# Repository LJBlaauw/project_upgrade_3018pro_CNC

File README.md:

# project_upgrade_3018pro_CNC

Het project is gebaseerd op opensource tools:
 - Freecad (3D parametrichs CAD)
 - Prusa slicer (3D printables voor Z unit en moerhouders
 - Kicad (PCB CAD ontwerp pico CNC, firmware GRBL webbuilder)
 - librecad (2D CAD)
 - GRBLHAL (GRBL uitbreiding voor diverse 32 bit processors)

# Dit project heft de tekort komingen van de Vevor S3018 Pro Max op

 1. Niet stijf genoeg De RVS geleiders buigen door.
 2. De Aluminium plaat is niet vlak.
 3. De spindel motor heeft een te klein vermogen.
 4. De gebruikte controller heeft de in en uitgangen direct naar buiten uitgevoerd, gevoelig voor storing.
 5. Geen eindschakelaars voor rustpositie.
 6. Te lichte XYZ motoren.
 7. Ondersteunt alleen GRBL.
 8. De moeren hebben backlash bij belasting.
 9. Geen Z-probe ingang
 10. Geen mist of Flood aansluiting

# aanpassingen

 1. Maakt gebruik van aluminium profielen en lineaire rails met blokken.
 2. gebruikt een vlakke stijve kunstof basis plaat.
 3. Maakt gebruik van een borstelloze spindle motor.
 4. Alle in en uitgangen worden gebufferd.
 5. WYZ eindschakelaars worden toegevoegd.
 6. De XYZmotoren zijn door zwaardere typen vervangen.
 7. Er is een nieuwe controller pico-CNC/GRBLHAL toegevoegd (RP2040 of RP2350, 64 bit).
 8. De XYZ-moeren worden nu gesteld zodat er geen backlash meer is.
 9. Aansluiting voor een touch plate of direct met de spindle
 10. ER zijn twee solid state uitgangen die direct uit de CNC router software aangestuurd kunnen worden.

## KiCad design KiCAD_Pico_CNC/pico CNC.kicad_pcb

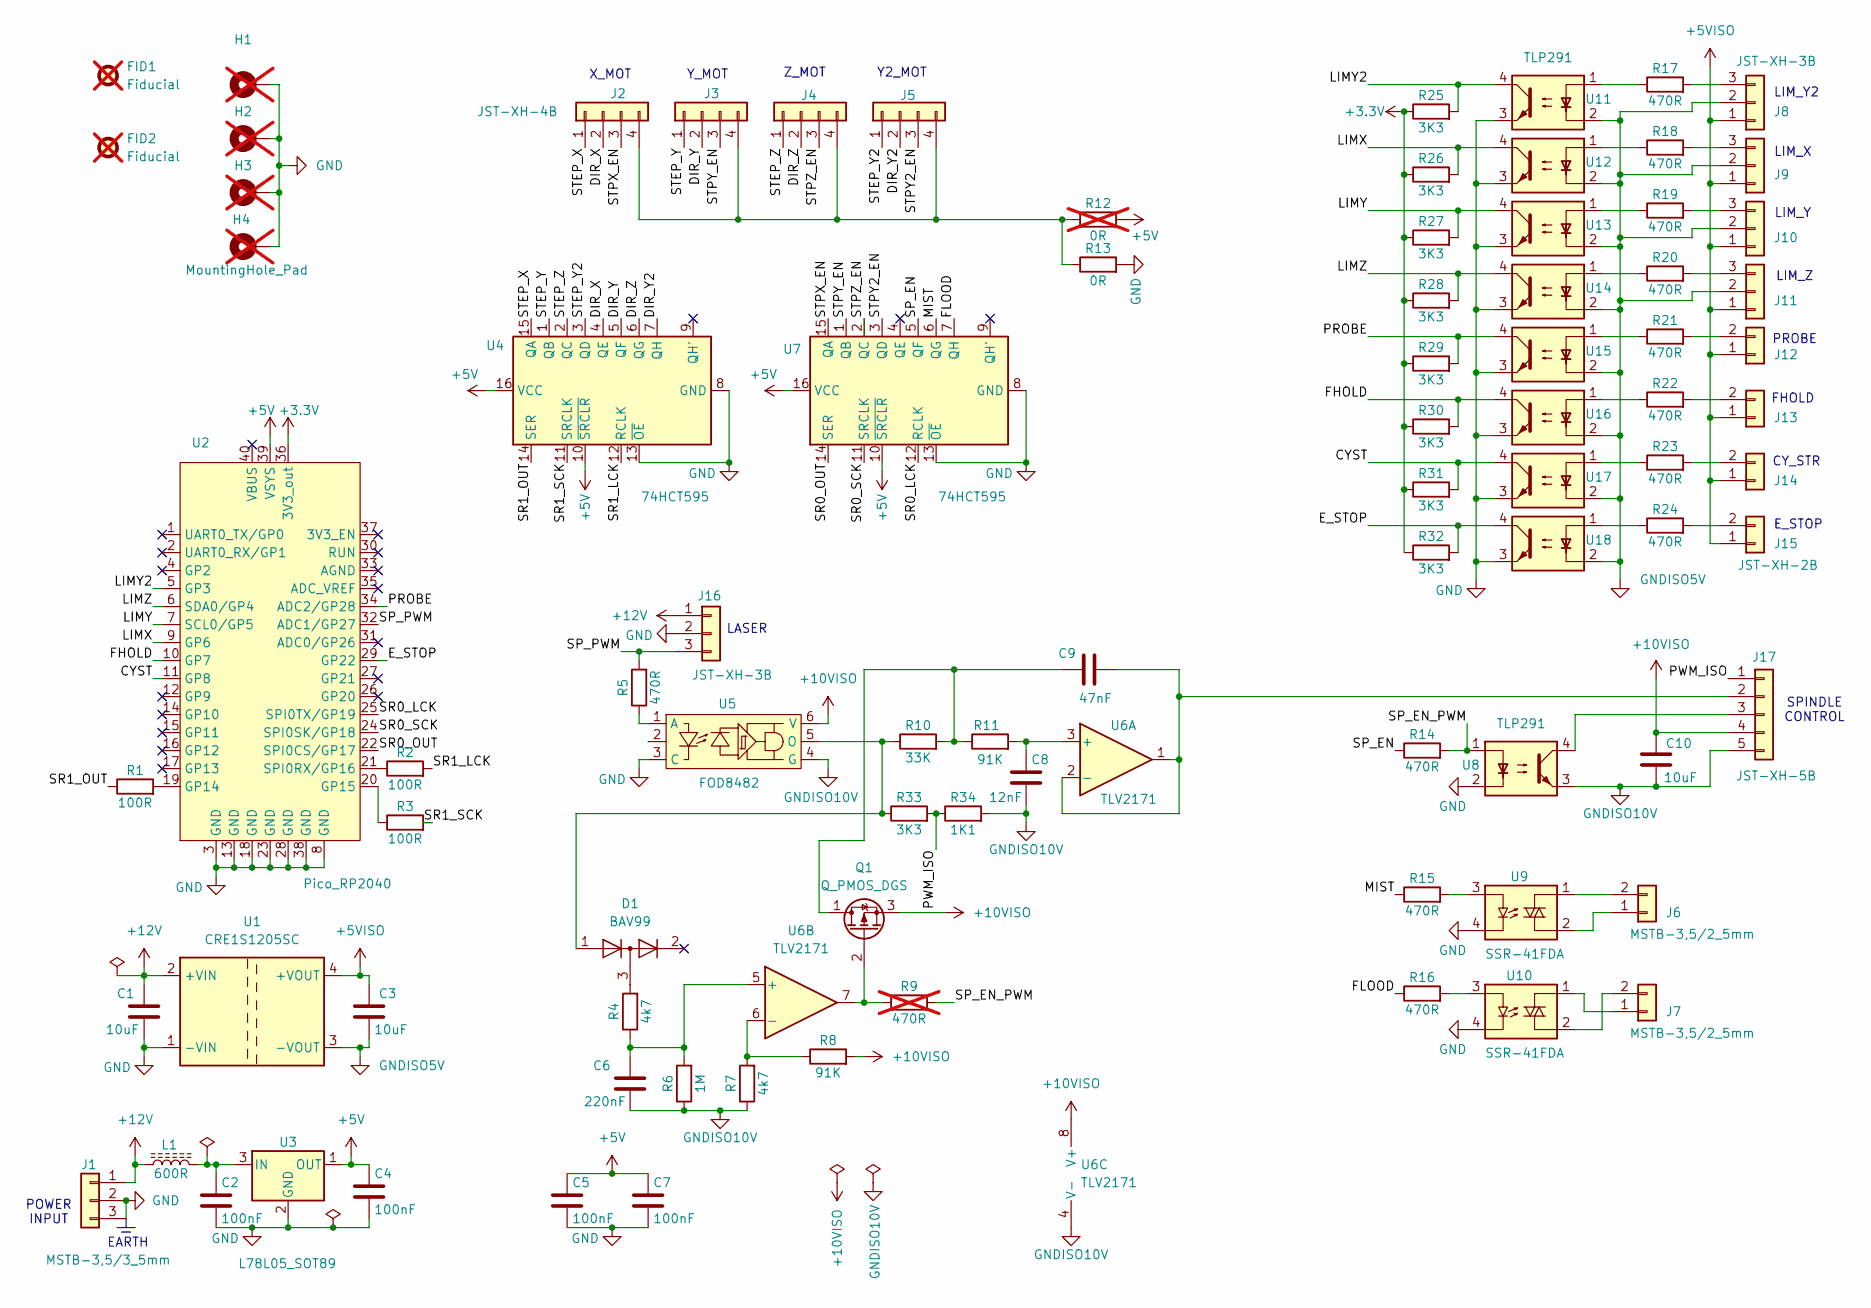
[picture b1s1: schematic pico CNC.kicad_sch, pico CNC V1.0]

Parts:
C1, C3, C10: 10uF; C_1206_3216Metric
C2, C4, C5, C7: 100nF; C_0805_2012Metric
C6: 220nF; C_0805_2012Metric
C8: 12nF; C_0805_2012Metric
C9: 47nF; C_0805_2012Metric
D1: BAV99; SOT-23
FID1, FID2: Fiducial; Fiducial_1mm_Mask2mm; not fitted
H1, H2, H3, H4: MountingHole_Pad; MountingHole_3.2mm_M3_Pad_Via; not fitted
J1: MSTB-3,5/3_5mm; PhoenixContact_MSTBA_2,5_3-G_1x03_P5.00mm_Horizontal
J2, J3, J4, J5: JST-XH-4B; JST_XH_B4B-XH-A_1x04_P2.50mm_Vertical
J6, J7: MSTB-3,5/2_5mm; PhoenixContact_MSTBA_2,5_2-G_1x02_P5.00mm_Horizontal
J8, J9, J10, J11, J16: JST-XH-3B; JST_XH_B3B-XH-A_1x03_P2.50mm_Vertical
J12, J13, J14, J15: JST-XH-2B; JST_XH_B2B-XH-A_1x02_P2.50mm_Vertical
J17: JST-XH-5B; JST_XH_B5B-XH-A_1x05_P2.50mm_Vertical
L1: 600R; L_0805_2012Metric
Q1: Q_PMOS_DGS
R1, R2, R3: 100R; R_0805_2012Metric
R4, R7: 4k7; R_0805_2012Metric
R5, R14, R15, R16, R17, R18, R19, R20, R21, R22, R23, R24: 470R; R_0805_2012Metric
R6: 1M; R_0805_2012Metric
R8, R11: 91K; R_0805_2012Metric
R9: 470R; R_0805_2012Metric; not fitted
R10: 33K; R_0805_2012Metric
R12: 0R; R_0805_2012Metric; not fitted
R13: 0R; R_0805_2012Metric
R25, R26, R27, R28, R29, R30, R31, R32, R33: 3K3; R_0805_2012Metric
R34: 1K1; R_0805_2012Metric
U1: CRE1S1205SC; Converter_DCDC_Murata_CRE1xxxxxxSC_THT
U2: Pico_RP2040
U3: L78L05_SOT89; SOT-89-3
U4, U7: 74HCT595; SOIC-16_3.9x9.9mm_P1.27mm
U5: FOD8482; SO-6L_10x3.84mm_P1.27mm
U6: TLV2171; SOIC-8_3.9x4.9mm_P1.27mm
U8, U11, U12, U13, U14, U15, U16, U17, U18: TLP291; TLP291 GB
U9, U10: SSR-41FDA

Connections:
+3.3V: R25.1, R26.1, R27.1, R28.1, R29.1, R30.1, R31.1, R32.1, U2.36 (3V3_out)
+5V: C4.1, C5.1, C7.1, R12.2, U2.39 (VSYS), U3.1 (OUT), U4.10 (~SRCLR), U4.16 (VCC), U7.10 (~SRCLR), U7.16 (VCC)
+5VISO: C3.1, J8.1, J9.1, J10.1, J11.1, J12.1, J13.1, J14.1, J15.1, U1.4 (+VOUT)
+10VISO: C10.1, J17.4, Q1.3 (S), R8.2, U5.6 (V), U6.8 (V+)
+12V: C1.1, J1.1, J16.1, L1.1, U1.2 (+VIN)
/CYST: R31.2, U2.11 (GP8), U17.4
/DIR_X: J2.2, U4.4 (QE)
/DIR_Y: J3.2, U4.5 (QF)
/DIR_Y2: J5.2, U4.7 (QH)
/DIR_Z: J4.2, U4.6 (QG)
/E_STOP: R32.2, U2.29 (GP22), U18.4
/FHOLD: R30.2, U2.10 (GP7), U16.4
/FLOOD: R16.1, U7.7 (QH)
/LIMX: R26.2, U2.9 (GP6), U12.4
/LIMY: R27.2, U2.7 (SCL0/GP5), U13.4
/LIMY2: R25.2, U2.5 (GP3), U11.4
/LIMZ: R28.2, U2.6 (SDA0/GP4), U14.4
/MIST: R15.1, U7.6 (QG)
/PROBE: R29.2, U2.34 (ADC2/GP28), U15.4
/PWM_ISO: J17.1, R33.2, R34.1
/SP_EN: R14.1, U7.5 (QF)
/SP_EN_PWM: R9.2, R14.2, U8.1
/SP_PWM: J16.3, R5.2, U2.32 (ADC1/GP27)
/SR0_LCK: U2.25 (SPI0TX/GP19), U7.12 (RCLK)
/SR0_OUT: U2.22 (SPI0CS/GP17), U7.14 (SER)
/SR0_SCK: U2.24 (SPI0SK/GP18), U7.11 (SRCLK)
/SR1_LCK: R2.2, U4.12 (RCLK)
/SR1_OUT: R1.1, U4.14 (SER)
/SR1_SCK: R3.2, U4.11 (SRCLK)
/STEP_X: J2.1, U4.15 (QA)
/STEP_Y: J3.1, U4.1 (QB)
/STEP_Y2: J5.1, U4.3 (QD)
/STEP_Z: J4.1, U4.2 (QC)
/STPX_EN: J2.3, U7.15 (QA)
/STPY2_EN: J5.3, U7.3 (QD)
/STPY_EN: J3.3, U7.1 (QB)
/STPZ_EN: J4.3, U7.2 (QC)
GND: C1.2, C2.2, C4.2, C5.2, C7.2, H1.1 (1_1), H2.1 (1_1), H3.1 (1_1), H4.1 (1_1), J1.2, J1.3, J16.2, R13.2, U1.1 (-VIN), U2.3 (GND), U2.8 (GND), U2.13 (GND), U2.18 (GND), U2.23 (GND), U2.28 (GND), U2.38 (GND), U3.2 (GND), U4.8 (GND), U4.13 (~OE), U5.3 (C), U7.8 (GND), U7.13 (~OE), U8.2, U9.4, U10.4, U11.3, U12.3, U13.3, U14.3, U15.3, U16.3, U17.3, U18.3
GNDISO5V: C3.2, J8.2, J9.2, J10.2, J11.2, U1.3 (-VOUT), U11.2, U12.2, U13.2, U14.2, U15.2, U16.2, U17.2, U18.2
GNDISO10V: C6.2, C8.2, C10.2, J17.5, R6.1, R7.1, R34.2, U5.4 (G), U6.4 (V-), U8.3
unnamed: D1.3 (K), R4.2
unnamed: J2.4, J3.4, J4.4, J5.4, R12.1, R13.1
unnamed: J6.1, U9.2
unnamed: J6.2, U9.1
unnamed: J7.1, U10.1
unnamed: J7.2, U10.2
unnamed: J8.3, R17.2
unnamed: J9.3, R18.2
unnamed: J10.3, R19.2
unnamed: J11.3, R20.2
unnamed: J12.2, R21.2
unnamed: J13.2, R22.2
unnamed: J14.2, R23.2
unnamed: J15.2, R24.2
unnamed: C9.2, J17.2, U6.1, U6.2 (-)
unnamed: J17.3, U8.4
unnamed: C9.1, Q1.1 (D), R10.2, R11.1
unnamed: Q1.2 (G), R9.1, U6.7
unnamed: R15.2, U9.3
unnamed: R16.2, U10.3
unnamed: R17.1, U11.1
unnamed: R18.1, U12.1
unnamed: R19.1, U13.1
unnamed: R20.1, U14.1
unnamed: R21.1, U15.1
unnamed: R22.1, U16.1
unnamed: R23.1, U17.1
unnamed: R24.1, U18.1
unnamed: R1.2, U2.19 (GP14)
unnamed: R3.1, U2.20 (GP15)
unnamed: R2.1, U2.21 (SPI0RX/GP16)
unnamed: C2.1, L1.2, U3.3 (IN)
unnamed: R5.1, U5.1 (A)
unnamed: D1.1 (K), R10.1, R33.1, U5.5 (O)
unnamed: C8.1, R11.2, U6.3 (+)
unnamed: C6.1, R4.1, R6.2, U6.5 (+)
unnamed: R7.2, R8.1, U6.6 (-)

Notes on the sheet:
Y_MOT
LASER
CY_STR
FHOLD
Z_MOT
Y2_MOT
PROBE
SPINDLE CONTROL
LIM_X
LIM_Y
LIM_Z
POWER INPUT
EARTH
E_STOP
X_MOT
LIM_Y2

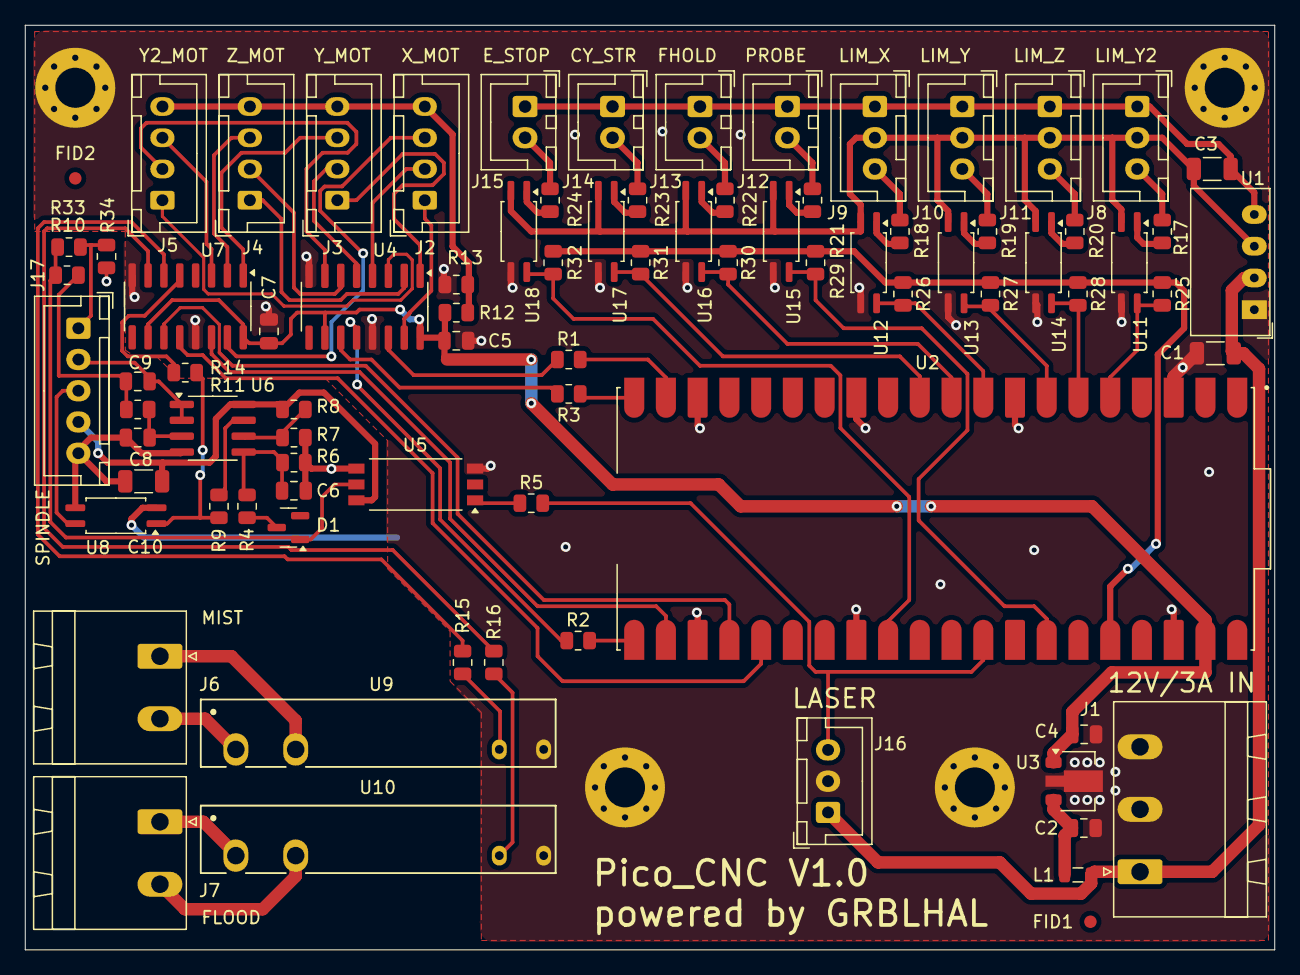
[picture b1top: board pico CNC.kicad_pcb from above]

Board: 2 copper layers, 100.0 x 74.0 mm, 87 parts (0 on the bottom side), 77 nets.

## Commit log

2026-06-21 Update README.md
    kleine toevoeging
